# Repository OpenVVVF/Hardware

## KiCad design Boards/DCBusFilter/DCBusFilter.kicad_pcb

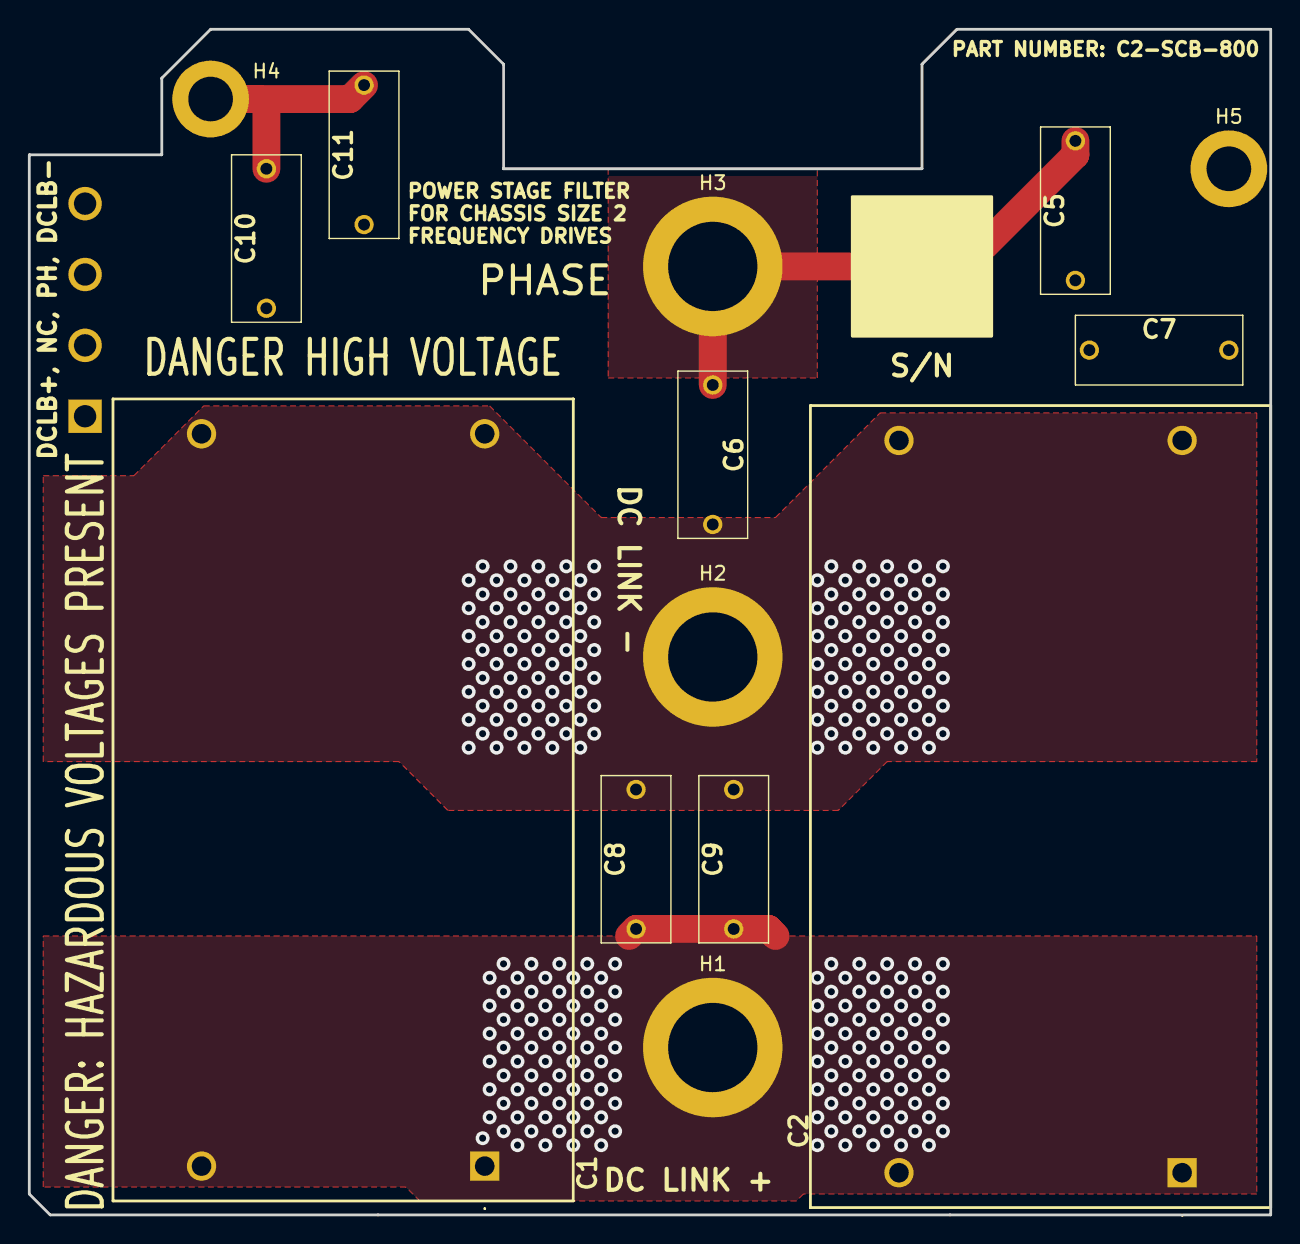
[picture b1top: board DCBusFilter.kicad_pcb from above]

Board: 4 copper layers, 89.0 x 85.0 mm, 15 parts (1 on the bottom side), 5 nets.

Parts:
C1, C2: MKP1848S61010JY5B
C5, C6, C7, C8, C9, C10, C11: VY1222M47Y5UQ6TV0
H1, H2, H3: MountingHole_Pad; MountingHole_6.4mm_M6_ISO14580_Pad
H4, H5: MountingHole_Pad; MountingHole_3.2mm_M3_ISO14580_Pad
J1: TBP01R2-508-04BE; SHDR4W100P0X508_1X4_2192X850X1200P

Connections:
/CHASSIS_GND: C10.1, C11.1, H4.1
/CHASSIS_GND_1: C7.1, H5.1
/DC_LINK_+: C1.1, C1.3, C2.1, C2.3, C5.2, C7.2, C8.2, C9.2, H1.1, J1.1
/DC_LINK_-: C1.2, C1.4, C2.2, C2.4, C6.1, C8.1, C9.1, C10.2, H2.1, J1.4
/PHASE_LEG: C5.1, C6.2, C11.2, H3.1, J1.3

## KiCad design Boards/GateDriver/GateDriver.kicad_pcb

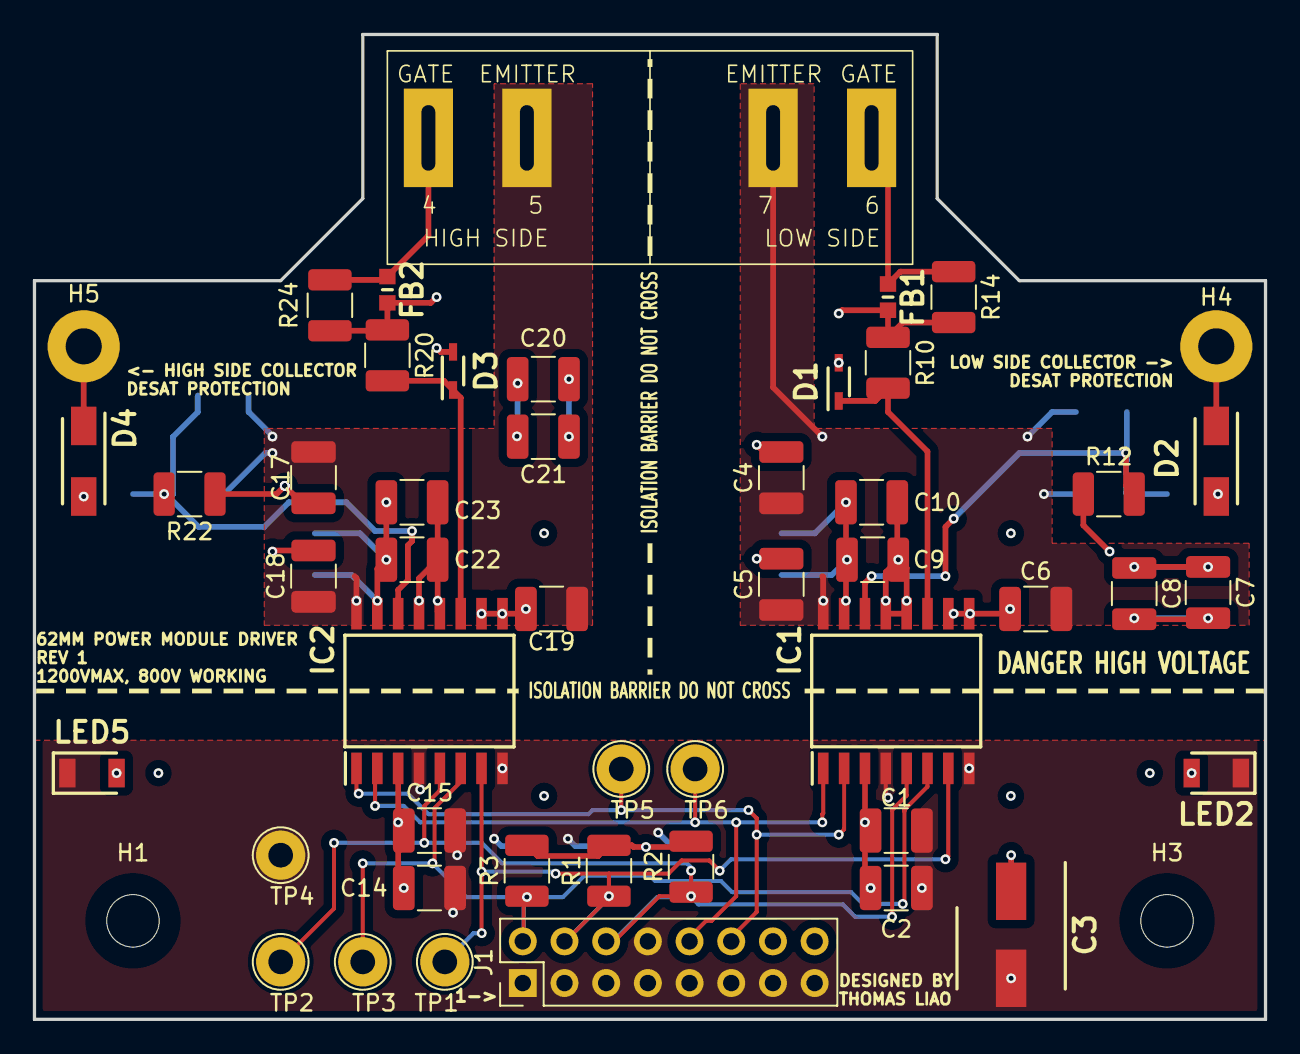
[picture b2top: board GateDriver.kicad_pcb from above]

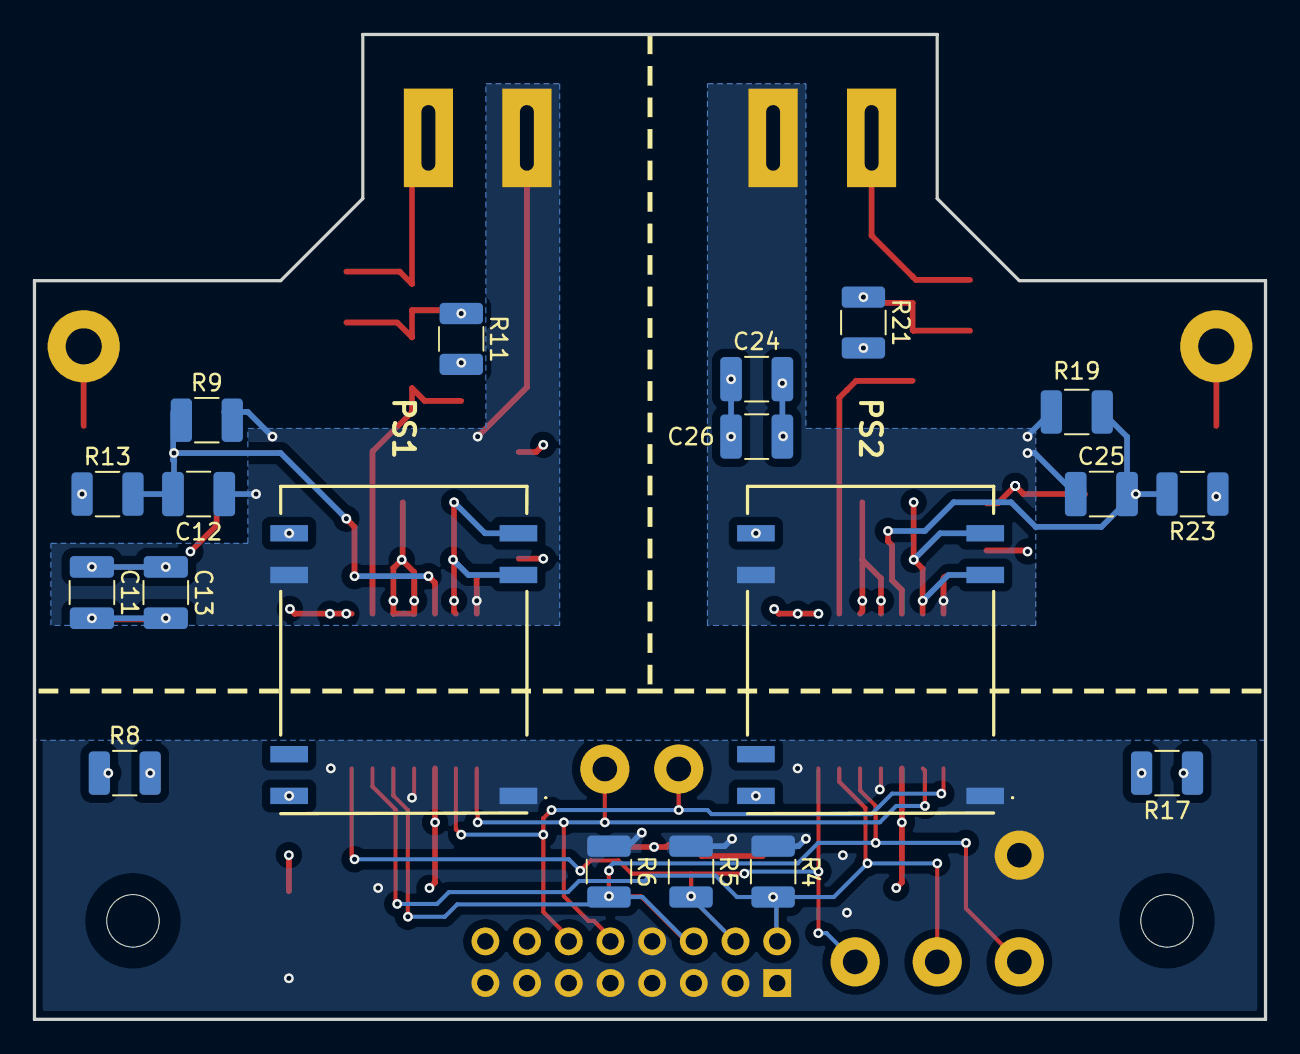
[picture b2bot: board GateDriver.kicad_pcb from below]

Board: 6 copper layers, 75.0 x 60.0 mm, 69 parts (19 on the bottom side), 30 nets.

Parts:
C1, C5, C6, C9, C12, C14, C18, C19, C22, C25: 100nF; C_1210_3225Metric_Pad1.33x2.70mm_HandSolder
C2, C4, C7, C8, C10, C11, C13, C15, C17, C20, C21, C23, C24, C26: 10uF; C_1210_3225Metric_Pad1.33x2.70mm_HandSolder
C3: UCM1H101MCL1GS; CAPAE660X800N
D1, D3: BAT54WS-7-F; SOD2513X120N
D2, D4: FM2000GP-TP; DIOM5226X244N
FB1, FB2: FBMJ1608HS220NTR; BEADC1608X100N
H1, H3: MountingHole; MountingHole_3.2mm_M3
H4, H5: MountingHole_Pad; MountingHole_2.2mm_M2_Pad
IC1, IC2: ADUM4136BRWZ; SOIC127P1032X265-16N
J1: Conn_02x08_Counter_Clockwise; PinHeader_2x08_P2.54mm_Vertical
LED2: LTST-C230CKT; LEDC3216X120N
LED5: LTST-C230GKT; LEDC3216X120N
PS1, PS2: MGJ2D121509MPC-R7; MGJ2D121509MPCR7
Q1: 62mm_power_module
R1, R2, R3, R4, R5, R6, R17: 4.7k; R_1210_3225Metric_Pad1.30x2.65mm_HandSolder
R8: 220; R_1210_3225Metric_Pad1.30x2.65mm_HandSolder
R9, R14, R19, R24: 0; R_1210_3225Metric_Pad1.30x2.65mm_HandSolder
R10, R20: 9.1; R_1210_3225Metric_Pad1.30x2.65mm_HandSolder
R11, R21: 6.8; R_1210_3225Metric_Pad1.30x2.65mm_HandSolder
R12, R13, R22, R23: 1k; R_1210_3225Metric_Pad1.30x2.65mm_HandSolder
TP1, TP2, TP3, TP4, TP5, TP6: TestPoint; TestPoint_Loop_D2.54mm_Drill1.5mm_Beaded

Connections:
/+3.3V_A: C1.2, C2.1, C14.2, C15.1, IC1.3 (VDD1), IC2.3 (VDD1), J1.14, R1.2, R2.2, R3.2, R8.2
/+12V_A: C3.1 (+), J1.16, PS1.8 (+VIN), PS2.8 (+VIN), R17.2
/FAULT: IC1.6 (~FAULT), IC2.6 (~FAULT), J1.2, R3.1, R4.2, TP3.1
/GND_A: C1.1, C2.2, C3.2 (-), C14.1, C15.2, IC1.4 (VSS1_1), IC1.8 (VSS1_2), IC2.4 (VSS1_1), IC2.8 (VSS1_2), J1.1, J1.3, J1.5, J1.7, J1.8, J1.9, J1.11, J1.13, J1.15, LED2.1 (K), LED5.1 (K), PS1.1 (-VIN), PS2.1 (-VIN), R4.1, R5.1, R6.1, TP4.1
/PH_H: IC1.2 (VI-), IC2.1 (VI+), J1.12, TP5.1
/PH_H_C: D4.1 (K), H5.1
/PH_H_G: FB2.1, Q1.3 (HIGH_GATE), R24.1
/PH_L: IC1.1 (VI+), IC2.2 (VI-), J1.10, TP6.1
/PH_L_C: D2.1 (K), H4.1
/PH_L_G: FB1.1, Q1.1 (LOW_GATE), R14.1
/READY: IC1.7 (READY), IC2.7 (READY), J1.4, R1.1, R5.2, TP1.1
/RESET: IC1.5 (~RESET), IC2.5 (~RESET), J1.6, R2.1, R6.2, TP2.1
/SingleChannelDriver1/+15V_B: C4.2, C5.2, C7.1, C8.1, C9.2, C10.1, C11.1, C13.1, IC1.12 (VDD2_1), IC1.13 (VDD2_2), PS1.5 (+VOUT), R12.1
/SingleChannelDriver1/-9V_B: C6.1, C7.2, C8.2, C9.1, C10.2, C11.2, C13.2, IC1.9 (VSS2_1), IC1.10 (VSS2_2), IC1.15 (VSS2_3), PS1.3 (-VOUT_1), PS1.4 (-VOUT_2)
/SingleChannelDriver1/GND_B: C4.1, C5.1, C6.2, C12.1, IC1.16 (GND2), PS1.6 (0V), Q1.2 (LOW_EMITTER), R9.2
/SingleChannelDriver/+15V_B: C17.2, C18.2, C20.1, C21.1, C22.2, C23.1, C24.1, C26.1, IC2.12 (VDD2_1), IC2.13 (VDD2_2), PS2.5 (+VOUT), R22.1
/SingleChannelDriver/-9V_B: C19.1, C20.2, C21.2, C22.1, C23.2, C24.2, C26.2, IC2.9 (VSS2_1), IC2.10 (VSS2_2), IC2.15 (VSS2_3), PS2.3 (-VOUT_1), PS2.4 (-VOUT_2)
/SingleChannelDriver/GND_B: C17.1, C18.1, C19.2, C25.1, IC2.16 (GND2), PS2.6 (0V), Q1.4 (HIGH_EMITTER), R19.2
unnamed: D1.2 (A), R11.2
unnamed: D1.1 (K), IC1.11 (VOUT), R10.2
unnamed: D2.2 (A), R13.1
unnamed: D3.2 (A), R21.2
unnamed: D3.1 (K), IC2.11 (VOUT), R20.2
unnamed: D4.2 (A), R23.1
unnamed: FB1.2, R10.1, R11.1, R14.2
unnamed: FB2.2, R20.1, R21.1, R24.2
unnamed: C12.2, IC1.14 (DESAT), R9.1, R12.2, R13.2
unnamed: C25.2, IC2.14 (DESAT), R19.1, R22.2, R23.2
unnamed: LED2.2 (A), R8.1
unnamed: LED5.2 (A), R17.1

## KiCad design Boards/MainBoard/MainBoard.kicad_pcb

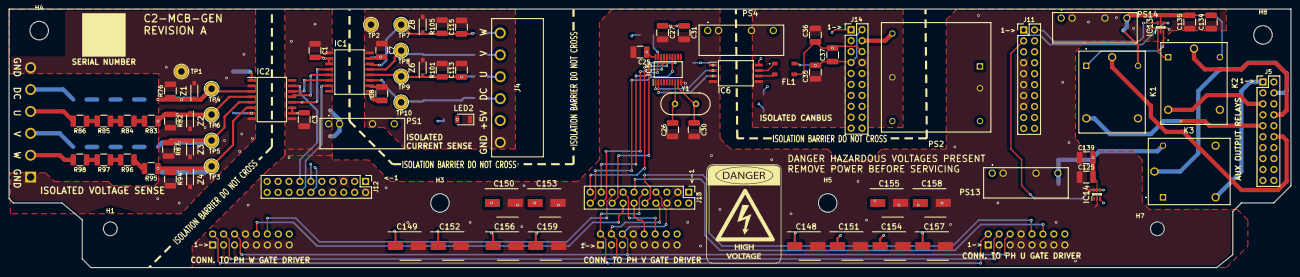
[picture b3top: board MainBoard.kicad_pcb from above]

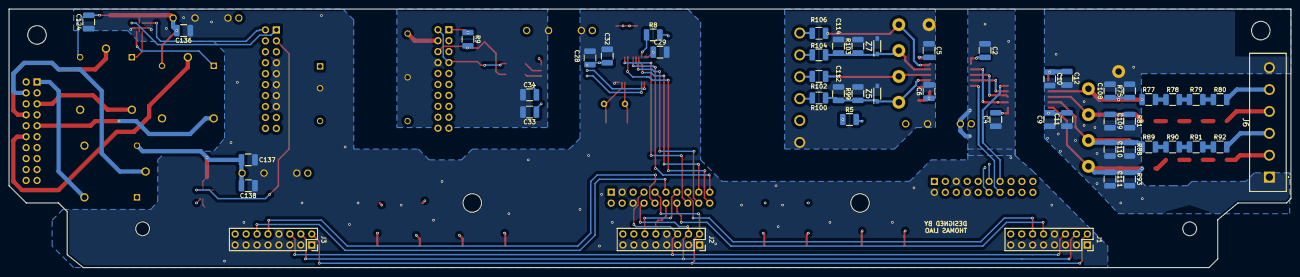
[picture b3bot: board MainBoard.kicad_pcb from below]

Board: 6 copper layers, 297.5 x 60.0 mm, 139 parts (50 on the bottom side), 85 nets.

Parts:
C1, C3, C5, C6, C9, C10, C25, C31, C32, C34: 100nF; C_1210_3225Metric_Pad1.33x2.70mm_HandSolder
C2, C4, C7, C8, C11, C12: 1uF; C_1210_3225Metric_Pad1.33x2.70mm_HandSolder
C26, C30, C35, C36, C37: 22pF; C_1210_3225Metric_Pad1.33x2.70mm_HandSolder
C27, C28, C29, C33, C124, C125, C134, C135, C136, C137, C138, C139: 10uF; C_1210_3225Metric_Pad1.33x2.70mm_HandSolder
C108, C109, C110, C111, C112, C113, C114, C115: 10nF; C_1210_3225Metric_Pad1.33x2.70mm_HandSolder
C148, C149, C150, C151, C152, C153, C154, C155, C156, C157, C158, C159: UCM1H101MCL1GS; CAPAE660X800N
FL1: ACT45B-101-2P-TL003; ACT45B1012PTL003
H1, H7: MountingHole; MountingHole_3.2mm_M3
H3, H4, H5, H8: MountingHole; MountingHole_4.3mm_M4
IC1, IC2: MAX22530AWE+; SOIC127P1032X265-16N
IC5: MCP2515-e_ST; SOP65P640X120-20N
IC6: ISO1042BDWVR; SOIC127P1150X280-8N
IC13, IC14: DRDNB21D-7; SOT65P210X110-6N
J1, J2, J3: Conn_02x08_Counter_Clockwise; PinSocket_2x08_P2.54mm_Vertical
J4: TBP01R1-508-06BE; TBP01R150806BE
J5, J11, J12, J13, J14: Conn_02x10_Counter_Clockwise; PinHeader_2x10_P2.54mm_Vertical
J6: TBP01R2-508-06BE; TBP01R250806BE
K1, K2, K3: AWHSH105D00G
LED2: LTST-C230CKT; LEDC3216X120N
PS1, PS4, PS13, PS14: RKE-1205S_H; RKE1205SH
PS2: REC10K-2424DAW_H2; REC10K-AW
R5, R76, R82, R88, R94, R99, R101, R103, R105: 1k; R_1210_3225Metric_Pad1.30x2.65mm_HandSolder
R8: 4.7k; R_1210_3225Metric_Pad1.30x2.65mm_HandSolder
R9: 120; R_1210_3225Metric_Pad1.30x2.65mm_HandSolder
R75, R81, R87, R93: 2k; R_1210_3225Metric_Pad1.30x2.65mm_HandSolder
R77, R78, R79, R80, R83, R84, R85, R86, R89, R90, R91, R92, R95, R96, R97, R98: 250k; R_1210_3225Metric_Pad1.30x2.65mm_HandSolder
R100, R102, R104, R106: 5k; R_1210_3225Metric_Pad1.30x2.65mm_HandSolder
TP1, TP2, TP3, TP4, TP5, TP6, TP7, TP8, TP9, TP10: TestPoint; TestPoint_Loop_D2.54mm_Drill1.5mm_Beaded
Y1: 8MHz; Crystal_HC49-4H_Vertical
Z1, Z2, Z3, Z4, Z5, Z6, Z7, Z8: SZMMSZ4678T1G; SOD3716X135N

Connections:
/+3.3V_A: C1.2, C2.2, C3.2, C4.2, C25.1, C28.2, C29.1, C32.1, C148.1 (+), C149.1 (+), C150.1 (+), C151.1 (+), IC1.10 (VDDPL), IC1.11 (VDDL), IC2.10 (VDDPL), IC2.11 (VDDL), IC5.20 (VDD), IC6.1 (VCC1), J1.14, J2.14, J3.14, J12.1, J12.4, J12.7, J13.1, J13.4, R8.2
/+5V_Y: J4.5, PS1.7 (+VOUT), R5.2
/+12V_A: C27.1, C31.1, C152.1 (+), C153.1 (+), C154.1 (+), C155.1 (+), C156.1 (+), C157.1 (+), C158.1 (+), C159.1 (+), J1.16, J2.16, J3.16, J11.6, J11.8, J11.10, J11.12, J11.14, J12.3, J12.6, J12.9, J13.2, J13.5, PS1.1 (+VIN), PS2.1 (+VIN), PS4.1 (+VIN), PS13.1 (+VIN), PS14.1 (+VIN)
/ADC_1/ADC2_5VFILTER_1/OUT: C112.1, IC1.3 (AIN1), R99.1, R100.1, TP10.1, Z5.1 (K)
/ADC_1/ADC2_5VFILTER_2/OUT: C113.1, IC1.4 (AIN2), R101.1, R102.1, TP9.1, Z6.1 (K)
/ADC_1/ADC2_5VFILTER_3/OUT: C114.1, IC1.5 (AIN3), R103.1, R104.1, TP8.1, Z7.1 (K)
/ADC_1/ADC2_5VFILTER_4/OUT: C115.1, IC1.6 (AIN4), R105.1, R106.1, TP7.1, Z8.1 (K)
/ADC_1/VoltageSenseInputStage1/LV_OUT: C109.1, IC2.4 (AIN2), R81.1, R82.1, R83.1, TP6.1, Z2.1 (K)
/ADC_1/VoltageSenseInputStage2/LV_OUT: C110.1, IC2.5 (AIN3), R87.1, R88.1, R89.1, TP5.1, Z3.1 (K)
/ADC_1/VoltageSenseInputStage3/LV_OUT: C111.1, IC2.6 (AIN4), R93.1, R94.1, R95.1, TP3.1, Z4.1 (K)
/ADC_1/VoltageSenseInputStage/LV_OUT: C108.1, IC2.3 (AIN1), R75.1, R76.1, R77.1, TP4.1, Z1.1 (K)
/CAN_5V_OUT: C33.1, C34.2, IC6.8 (VCC2), PS4.7 (+VOUT)
/CAN_24V_OUT: J14.4, PS2.6 (+VOUT)
/CAN_GND: C33.2, C34.1, C35.1, C36.2, IC6.5 (GND2), J14.8, PS2.5 (COM), PS4.5 (-VOUT)
/CAN_HIGH: C35.2, C37.1, FL1.4, J14.2, J14.7
/CAN_JUMPER_B: J14.1, R9.1
/CAN_LOW: C36.1, C37.2, FL1.3, J14.6, R9.2
/DC_LINK_VSENSE_U: J6.5, R80.2
/FAULT: J1.2, J2.2, J3.2, J13.9
/GND_A: C1.1, C2.1, C3.1, C4.1, C25.2, C26.2, C27.2, C28.1, C29.2, C30.2, C31.2, C32.2, C124.1, C125.1, C134.1, C135.1, C136.1, C137.1, C138.1, C139.1, C148.2 (-), C149.2 (-), C150.2 (-), C151.2 (-), C152.2 (-), C153.2 (-), C154.2 (-), C155.2 (-), C156.2 (-), C157.2 (-), C158.2 (-), C159.2 (-), IC1.9 (GNDL), IC2.9 (GNDL), IC5.10 (VSS), IC6.4 (GND1), IC13.2 (E1/E2), IC14.2 (E1/E2), IC14.6 (B1), J1.1, J1.3, J1.5, J1.7, J1.8, J1.9, J1.11, J1.13, J1.15, J2.1, J2.3, J2.5, J2.7, J2.8, J2.9, J2.11, J2.13, J2.15, J3.1, J3.3, J3.5, J3.7, J3.8, J3.9, J3.11, J3.13, J3.15, J11.7, J11.9, J11.11, J11.13, J11.15, J12.2, J12.5, J12.8, J13.3, J13.6, PS1.2 (-VIN), PS2.2 (-VIN), PS4.2 (-VIN), PS13.2 (-VIN), PS13.5 (-VOUT), PS14.2 (-VIN), PS14.5 (-VOUT)
/GND_U: C9.1, C10.2, C11.1, C12.2, C108.2, C109.2, C110.2, C111.2, IC2.2 (AGND), IC2.8 (GNDF), J6.1, J6.6, R75.2, R76.2, R81.2, R82.2, R87.2, R88.2, R93.2, R94.2, TP1.1, Z1.2 (A), Z2.2 (A), Z3.2 (A), Z4.2 (A)
/ISENSE_DC_LINK_Y: J4.4, R100.2
/ISENSE_GND_Y: C5.1, C6.2, C7.1, C8.2, C112.2, C113.2, C114.2, C115.2, IC1.2 (AGND), IC1.8 (GNDF), J4.6, LED2.1 (K), PS1.5 (-VOUT), R99.2, R101.2, R103.2, R105.2, TP2.1, Z5.2 (A), Z6.2 (A), Z7.2 (A), Z8.2 (A)
/ISENSE_PH_U_Y: J4.3, R102.2
/ISENSE_PH_V_Y: J4.2, R104.2
/ISENSE_PH_W_Y: J4.1, R106.2
/OutputRelays/+5V_A_INT: C125.2, C137.2, C138.2, C139.2, IC14.5 (K1/K2), K3.4 (COIL_2), PS13.7 (+VOUT)
/OutputRelays/+5V_A_INT_2: C124.2, C134.2, C135.2, C136.2, IC13.5 (K1/K2), K1.4 (COIL_2), K2.4 (COIL_2), PS14.7 (+VOUT)
/PH_U_H: J1.12, J13.15
/PH_U_L: J1.10, J13.14
/PH_U_VSENSE_U: J6.4, R86.2
/PH_V_H: J2.12, J13.13
/PH_V_L: J2.10, J13.12
/PH_V_VSENSE_U: J6.3, R92.2
/PH_W_H: J3.12, J13.11
/PH_W_L: J3.10, J13.10
/PH_W_VSENSE_U: J6.2, R98.2
/READY: J1.4, J2.4, J3.4, J13.8
/RELAY1_COM: J5.12, K1.5 (COM)
/RELAY1_NO: J5.9, K1.2 (NO)
/RELAY2_COM: J5.8, K2.5 (COM)
/RELAY2_NO: J5.5, K2.2 (NO)
/RELAY3_COM: J5.4, K3.5 (COM)
/RELAY3_NO: J5.1, K3.2 (NO)
/RELAY_1_A: IC13.4 (B2), J11.1
/RELAY_2_A: IC13.6 (B1), J11.2
/RELAY_3_A: IC14.4 (B2), J11.3
/RESET: J1.6, J2.6, J3.6, J13.7
/SPI1_CAN_CS_A: IC5.18 (~CS), J13.17
/SPI1_CAN_INT_A: IC5.13 (~INT), J13.16
/SPI1_RX_A: IC5.17 (SO), J13.18
/SPI1_SCK_A: IC5.14 (SCK), J13.20
/SPI1_TX_A: IC5.16 (SI), J13.19
/SPI2_ADC1_CS_A: IC2.15 (~CS), J12.13
/SPI2_ADC2_CS_A: IC1.15 (~CS), J12.14
/SPI2_RX_A: IC1.12 (SDO), IC2.12 (SDO), J12.10
/SPI2_SCK_A: IC1.14 (SCLK), IC2.14 (SCLK), J12.12
/SPI2_TX_A: IC1.13 (SDI), IC2.13 (SDI), J12.11
unnamed: C6.1, C8.1, IC1.1 (REF)
unnamed: C5.2, C7.2, IC1.7 (VDDF)
unnamed: C10.1, C12.1, IC2.1 (REF)
unnamed: C9.2, C11.2, IC2.7 (VDDF)
unnamed: C30.1, IC5.9 (OSC1), Y1.2
unnamed: C26.1, IC5.8 (OSC2), Y1.1
unnamed: IC5.2 (RXCAN), IC6.3 (RXD)
unnamed: IC5.1 (TXCAN), IC6.2 (TXD)
unnamed: IC5.19 (~RESET), R8.1
unnamed: FL1.1, IC6.7 (CANH)
unnamed: FL1.2, IC6.6 (CANL)
unnamed: IC13.1 (C1/A1), K2.1 (COIL_1)
unnamed: IC13.3 (C2/A2), K1.1 (COIL_1)
unnamed: IC14.3 (C2/A2), K3.1 (COIL_1)
unnamed: LED2.2 (A), R5.1
unnamed: R77.2, R78.1
unnamed: R78.2, R79.1
unnamed: R79.2, R80.1
unnamed: R83.2, R84.1
unnamed: R84.2, R85.1
unnamed: R85.2, R86.1
unnamed: R89.2, R90.1
unnamed: R90.2, R91.1
unnamed: R91.2, R92.1
unnamed: R95.2, R96.1
unnamed: R96.2, R97.1
unnamed: R97.2, R98.1

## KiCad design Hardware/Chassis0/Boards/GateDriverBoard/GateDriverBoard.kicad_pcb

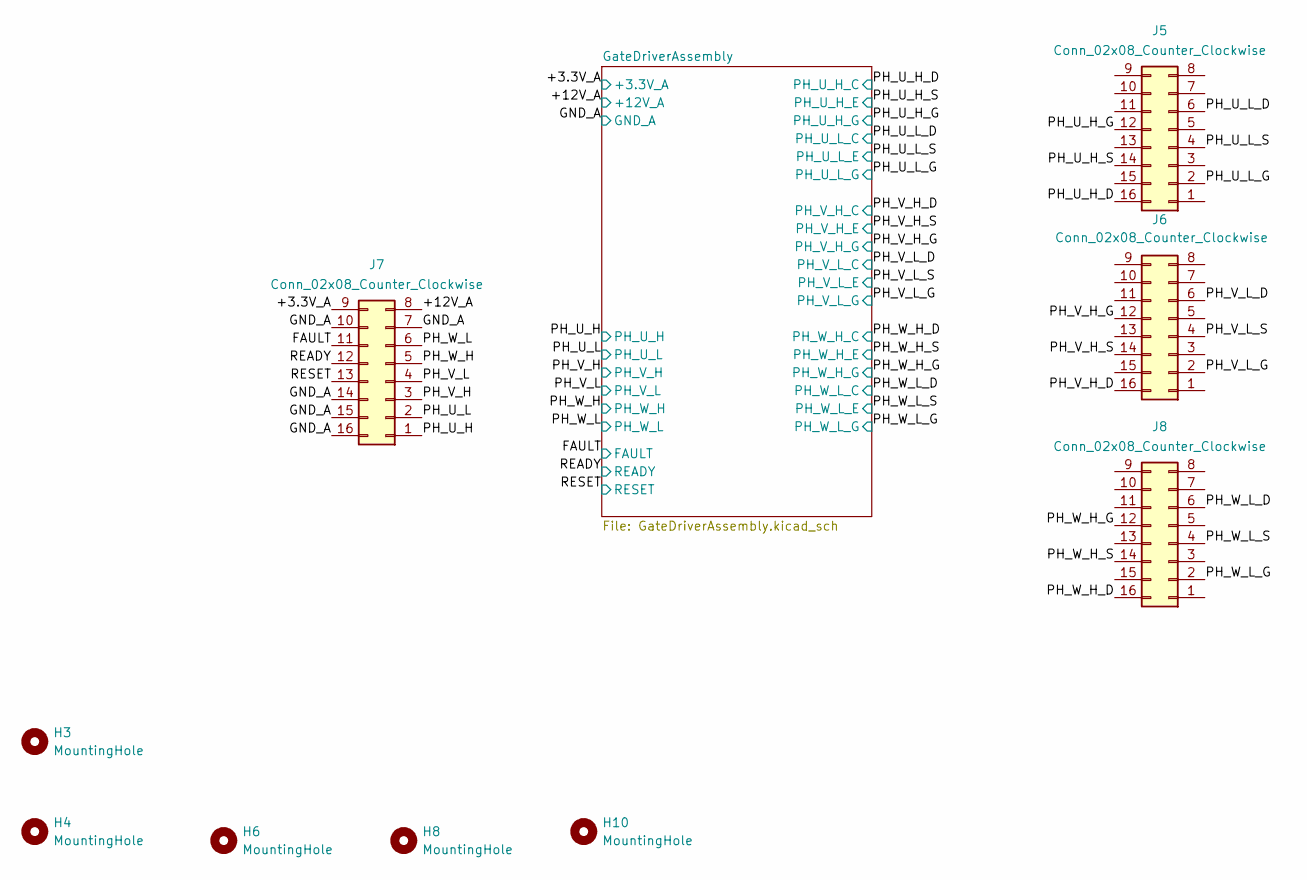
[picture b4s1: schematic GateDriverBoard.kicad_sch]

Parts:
H3, H4, H6, H8, H10: MountingHole; MountingHole_4.3mm_M4
J5, J6, J7, J8: Conn_02x08_Counter_Clockwise; PinSocket_2x08_P2.54mm_Vertical

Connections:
/+3.3V_A: J7.9; also elsewhere on the board
/+12V_A: J7.8; also elsewhere on the board
/FAULT: J7.11; also elsewhere on the board
/GND_A: J7.7, J7.10, J7.14, J7.15, J7.16; also elsewhere on the board
/PH_U_H: J7.1; also elsewhere on the board
/PH_U_H_D: J5.16; also elsewhere on the board
/PH_U_H_G: J5.12; also elsewhere on the board
/PH_U_H_S: J5.14; also elsewhere on the board
/PH_U_L: J7.2; also elsewhere on the board
/PH_U_L_D: J5.6; also elsewhere on the board
/PH_U_L_G: J5.2; also elsewhere on the board
/PH_U_L_S: J5.4; also elsewhere on the board
/PH_V_H: J7.3; also elsewhere on the board
/PH_V_H_D: J6.16; also elsewhere on the board
/PH_V_H_G: J6.12; also elsewhere on the board
/PH_V_H_S: J6.14; also elsewhere on the board
/PH_V_L: J7.4; also elsewhere on the board
/PH_V_L_D: J6.6; also elsewhere on the board
/PH_V_L_G: J6.2; also elsewhere on the board
/PH_V_L_S: J6.4; also elsewhere on the board
/PH_W_H: J7.5; also elsewhere on the board
/PH_W_H_D: J8.16; also elsewhere on the board
/PH_W_H_G: J8.12; also elsewhere on the board
/PH_W_H_S: J8.14; also elsewhere on the board
/PH_W_L: J7.6; also elsewhere on the board
/PH_W_L_D: J8.6; also elsewhere on the board
/PH_W_L_G: J8.2; also elsewhere on the board
/PH_W_L_S: J8.4; also elsewhere on the board
/READY: J7.12; also elsewhere on the board
/RESET: J7.13; also elsewhere on the board

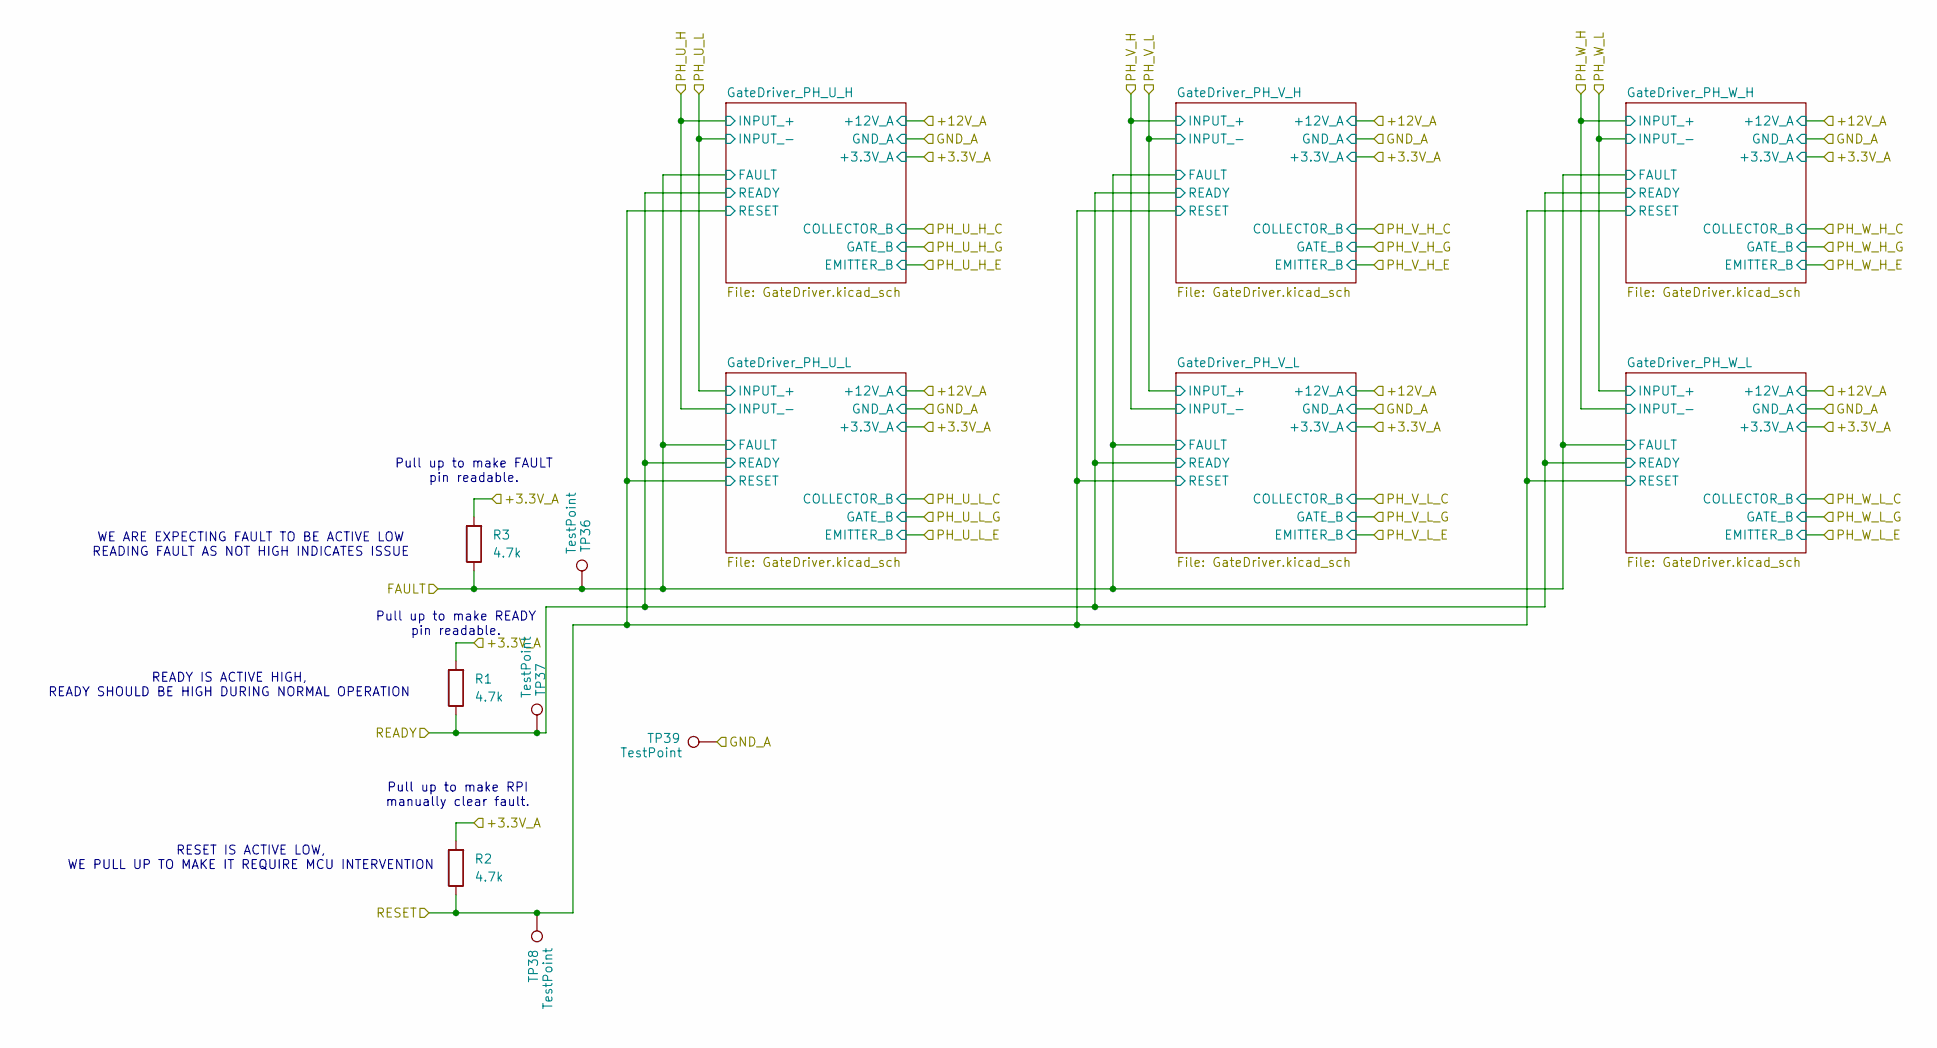
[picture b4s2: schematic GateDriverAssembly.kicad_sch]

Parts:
R1, R2, R3: 4.7k; R_1210_3225Metric_Pad1.30x2.65mm_HandSolder
TP36, TP37, TP38, TP39: TestPoint; TestPoint_Loop_D2.54mm_Drill1.5mm_Beaded

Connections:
/+3.3V_A: R1.2, R2.2, R3.2; also elsewhere on the board
/FAULT: R3.1, TP36.1; also elsewhere on the board
/GND_A: TP39.1; also elsewhere on the board
/READY: R1.1, TP37.1; also elsewhere on the board
/RESET: R2.1, TP38.1; also elsewhere on the board

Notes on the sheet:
READY IS ACTIVE HIGH, READY SHOULD BE HIGH DURING NORMAL OPERATION
Pull up to make READY pin readable.
WE ARE EXPECTING FAULT TO BE ACTIVE LOW READING FAULT AS NOT HIGH INDICATES ISSUE
Pull up to make FAULT pin readable.
Pull up to make RPI manually clear fault.
RESET IS ACTIVE LOW, WE PULL UP TO MAKE IT REQUIRE MCU INTERVENTION

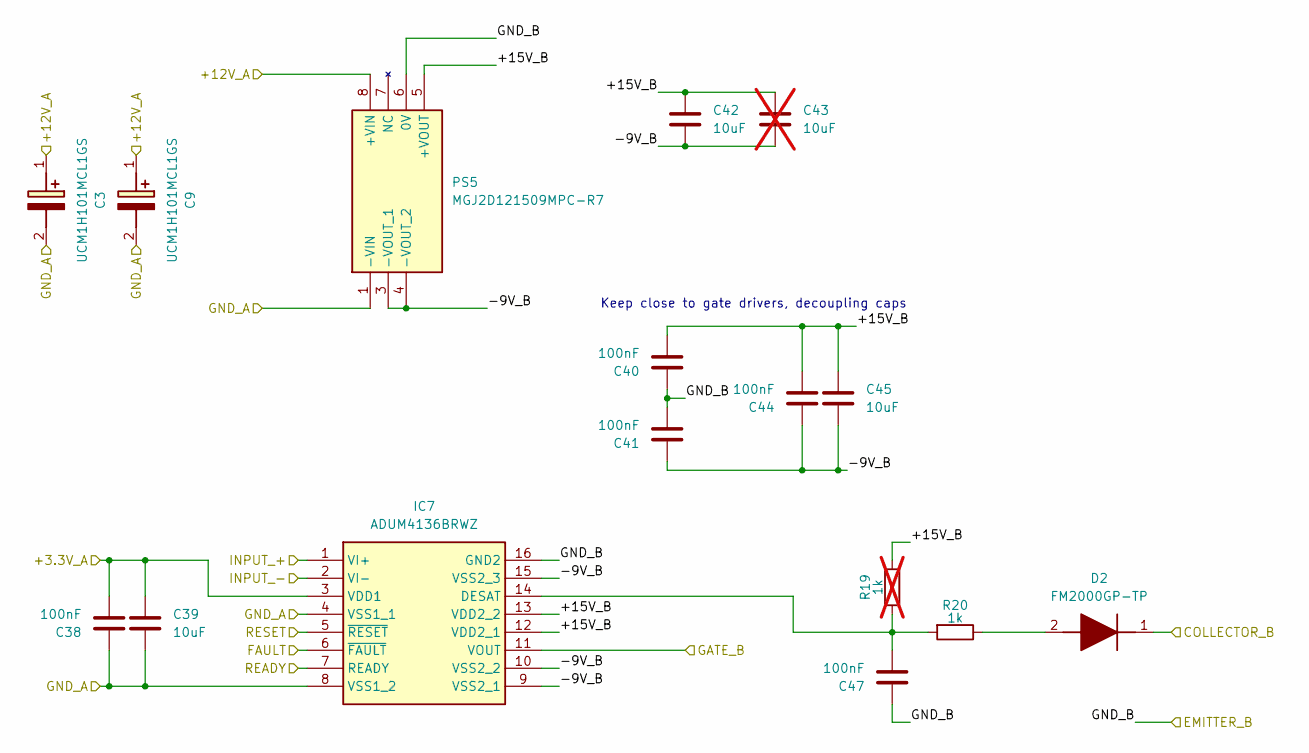
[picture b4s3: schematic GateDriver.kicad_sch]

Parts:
C3, C9: UCM1H101MCL1GS; CAPAE660X800N; Mouser Part Number 647-UCM1H101MCL1GS
C38, C40, C41, C44, C47: 100nF; C_1210_3225Metric_Pad1.33x2.70mm_HandSolder
C39, C42, C45: 10uF; C_1210_3225Metric_Pad1.33x2.70mm_HandSolder
C43: 10uF; C_1210_3225Metric_Pad1.33x2.70mm_HandSolder; not fitted
D2: FM2000GP-TP; DIOM5226X244N; Mouser Part Number 833-FM2000GP-TP
IC7: ADUM4136BRWZ; SOIC127P1032X265-16N; Mouser Part Number 584-ADUM4136BRWZ
PS5: MGJ2D121509MPC-R7; MGJ2D121509MPCR7; Mouser Part Number 580-MGJ2D121509MPCR7
R19: 1k; R_1210_3225Metric_Pad1.30x2.65mm_HandSolder; not fitted
R20: 1k; R_1210_3225Metric_Pad1.30x2.65mm_HandSolder

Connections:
/+3.3V_A: C38.2, C39.1, IC7.3 (VDD1); also elsewhere on the board
/+12V_A: C3.1 (+), C9.1 (+), PS5.8 (+VIN); also elsewhere on the board
/FAULT: IC7.6 (~FAULT); also elsewhere on the board
/GND_A: C3.2 (-), C9.2 (-), C38.1, C39.2, IC7.4 (VSS1_1), IC7.8 (VSS1_2), PS5.1 (-VIN); also elsewhere on the board
/GateDriverAssembly/GateDriver_PH_U_H/+15V_B: C40.2, C42.1, C43.1, C44.2, C45.1, IC7.12 (VDD2_1), IC7.13 (VDD2_2), PS5.5 (+VOUT), R19.1
/GateDriverAssembly/GateDriver_PH_U_H/-9V_B: C41.1, C42.2, C43.2, C44.1, C45.2, IC7.9 (VSS2_1), IC7.10 (VSS2_2), IC7.15 (VSS2_3), PS5.3 (-VOUT_1), PS5.4 (-VOUT_2)
/PH_U_H: IC7.1 (VI+); also elsewhere on the board
/PH_U_H_D: D2.1 (K); also elsewhere on the board
/PH_U_H_G: IC7.11 (VOUT); also elsewhere on the board
/PH_U_H_S: C40.1, C41.2, C47.1, IC7.16 (GND2), PS5.6 (0V); also elsewhere on the board
/PH_U_L: IC7.2 (VI-); also elsewhere on the board
/READY: IC7.7 (READY); also elsewhere on the board
/RESET: IC7.5 (~RESET); also elsewhere on the board
unnamed: D2.2 (A), R20.1
unnamed: C47.2, IC7.14 (DESAT), R19.2, R20.2

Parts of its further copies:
C4, C5, C6, C7, C8, C10, C11, C12, C13, C14: UCM1H101MCL1GS; CAPAE660X800N; Mouser Part Number 647-UCM1H101MCL1GS
C53, C55, C56, C59, C62, C64, C66, C67, C70, C73, C75, C77, C78, C81, C84, C86, C88, C89, C92, C95, C97, C99, C100, C103, C106: 100nF; C_1210_3225Metric_Pad1.33x2.70mm_HandSolder
C54, C57, C60, C65, C68, C71, C76, C79, C82, C87, C90, C93, C98, C101, C104: 10uF; C_1210_3225Metric_Pad1.33x2.70mm_HandSolder
C58, C69, C80, C91, C102: 10uF; C_1210_3225Metric_Pad1.33x2.70mm_HandSolder; not fitted
D7, D9, D11, D13, D14: FM2000GP-TP; DIOM5226X244N; Mouser Part Number 833-FM2000GP-TP
IC8, IC9, IC10, IC11, IC12: ADUM4136BRWZ; SOIC127P1032X265-16N; Mouser Part Number 584-ADUM4136BRWZ
PS8, PS9, PS10, PS11, PS12: MGJ2D121509MPC-R7; MGJ2D121509MPCR7; Mouser Part Number 580-MGJ2D121509MPCR7
R30, R40, R50, R60, R70: 1k; R_1210_3225Metric_Pad1.30x2.65mm_HandSolder; not fitted
R31, R41, R51, R61, R71: 1k; R_1210_3225Metric_Pad1.30x2.65mm_HandSolder

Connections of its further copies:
/+3.3V_A: C53.2, C54.1, C64.2, C65.1, C75.2, C76.1, C86.2, C87.1, C97.2, C98.1, IC8.3 (VDD1), IC9.3 (VDD1), IC10.3 (VDD1), IC11.3 (VDD1), IC12.3 (VDD1); also elsewhere on the board
/+12V_A: C4.1 (+), C5.1 (+), C6.1 (+), C7.1 (+), C8.1 (+), C10.1 (+), C11.1 (+), C12.1 (+), C13.1 (+), C14.1 (+), PS8.8 (+VIN), PS9.8 (+VIN), PS10.8 (+VIN), PS11.8 (+VIN), PS12.8 (+VIN); also elsewhere on the board
/FAULT: IC8.6 (~FAULT), IC9.6 (~FAULT), IC10.6 (~FAULT), IC11.6 (~FAULT), IC12.6 (~FAULT); also elsewhere on the board
/GND_A: C4.2 (-), C5.2 (-), C6.2 (-), C7.2 (-), C8.2 (-), C10.2 (-), C11.2 (-), C12.2 (-), C13.2 (-), C14.2 (-), C53.1, C54.2, C64.1, C65.2, C75.1, C76.2, C86.1, C87.2, C97.1, C98.2, IC8.4 (VSS1_1), IC8.8 (VSS1_2), IC9.4 (VSS1_1), IC9.8 (VSS1_2), IC10.4 (VSS1_1), IC10.8 (VSS1_2), IC11.4 (VSS1_1), IC11.8 (VSS1_2), IC12.4 (VSS1_1), IC12.8 (VSS1_2), PS8.1 (-VIN), PS9.1 (-VIN), PS10.1 (-VIN), PS11.1 (-VIN), PS12.1 (-VIN); also elsewhere on the board
/GateDriverAssembly/GateDriver_PH_U_L/+15V_B: C55.2, C57.1, C58.1, C59.2, C60.1, IC8.12 (VDD2_1), IC8.13 (VDD2_2), PS8.5 (+VOUT), R30.1
/GateDriverAssembly/GateDriver_PH_U_L/-9V_B: C56.1, C57.2, C58.2, C59.1, C60.2, IC8.9 (VSS2_1), IC8.10 (VSS2_2), IC8.15 (VSS2_3), PS8.3 (-VOUT_1), PS8.4 (-VOUT_2)
/GateDriverAssembly/GateDriver_PH_V_H/+15V_B: C66.2, C68.1, C69.1, C70.2, C71.1, IC9.12 (VDD2_1), IC9.13 (VDD2_2), PS9.5 (+VOUT), R40.1
/GateDriverAssembly/GateDriver_PH_V_H/-9V_B: C67.1, C68.2, C69.2, C70.1, C71.2, IC9.9 (VSS2_1), IC9.10 (VSS2_2), IC9.15 (VSS2_3), PS9.3 (-VOUT_1), PS9.4 (-VOUT_2)
/GateDriverAssembly/GateDriver_PH_V_L/+15V_B: C77.2, C79.1, C80.1, C81.2, C82.1, IC10.12 (VDD2_1), IC10.13 (VDD2_2), PS10.5 (+VOUT), R50.1
/GateDriverAssembly/GateDriver_PH_V_L/-9V_B: C78.1, C79.2, C80.2, C81.1, C82.2, IC10.9 (VSS2_1), IC10.10 (VSS2_2), IC10.15 (VSS2_3), PS10.3 (-VOUT_1), PS10.4 (-VOUT_2)
/GateDriverAssembly/GateDriver_PH_W_H/+15V_B: C88.2, C90.1, C91.1, C92.2, C93.1, IC11.12 (VDD2_1), IC11.13 (VDD2_2), PS11.5 (+VOUT), R60.1
/GateDriverAssembly/GateDriver_PH_W_H/-9V_B: C89.1, C90.2, C91.2, C92.1, C93.2, IC11.9 (VSS2_1), IC11.10 (VSS2_2), IC11.15 (VSS2_3), PS11.3 (-VOUT_1), PS11.4 (-VOUT_2)
/GateDriverAssembly/GateDriver_PH_W_L/+15V_B: C99.2, C101.1, C102.1, C103.2, C104.1, IC12.12 (VDD2_1), IC12.13 (VDD2_2), PS12.5 (+VOUT), R70.1
/GateDriverAssembly/GateDriver_PH_W_L/-9V_B: C100.1, C101.2, C102.2, C103.1, C104.2, IC12.9 (VSS2_1), IC12.10 (VSS2_2), IC12.15 (VSS2_3), PS12.3 (-VOUT_1), PS12.4 (-VOUT_2)
/PH_U_H: IC8.2 (VI-); also elsewhere on the board
/PH_U_L: IC8.1 (VI+); also elsewhere on the board
/PH_U_L_D: D14.1 (K); also elsewhere on the board
/PH_U_L_G: IC8.11 (VOUT); also elsewhere on the board
/PH_U_L_S: C55.1, C56.2, C62.1, IC8.16 (GND2), PS8.6 (0V); also elsewhere on the board
/PH_V_H: IC9.1 (VI+), IC10.2 (VI-); also elsewhere on the board
/PH_V_H_D: D7.1 (K); also elsewhere on the board
/PH_V_H_G: IC9.11 (VOUT); also elsewhere on the board
/PH_V_H_S: C66.1, C67.2, C73.1, IC9.16 (GND2), PS9.6 (0V); also elsewhere on the board
/PH_V_L: IC9.2 (VI-), IC10.1 (VI+); also elsewhere on the board
/PH_V_L_D: D9.1 (K); also elsewhere on the board
/PH_V_L_G: IC10.11 (VOUT); also elsewhere on the board
/PH_V_L_S: C77.1, C78.2, C84.1, IC10.16 (GND2), PS10.6 (0V); also elsewhere on the board
/PH_W_H: IC11.1 (VI+), IC12.2 (VI-); also elsewhere on the board
/PH_W_H_D: D11.1 (K); also elsewhere on the board
/PH_W_H_G: IC11.11 (VOUT); also elsewhere on the board
/PH_W_H_S: C88.1, C89.2, C95.1, IC11.16 (GND2), PS11.6 (0V); also elsewhere on the board
/PH_W_L: IC11.2 (VI-), IC12.1 (VI+); also elsewhere on the board
/PH_W_L_D: D13.1 (K); also elsewhere on the board
/PH_W_L_G: IC12.11 (VOUT); also elsewhere on the board
/PH_W_L_S: C99.1, C100.2, C106.1, IC12.16 (GND2), PS12.6 (0V); also elsewhere on the board
/READY: IC8.7 (READY), IC9.7 (READY), IC10.7 (READY), IC11.7 (READY), IC12.7 (READY); also elsewhere on the board
/RESET: IC8.5 (~RESET), IC9.5 (~RESET), IC10.5 (~RESET), IC11.5 (~RESET), IC12.5 (~RESET); also elsewhere on the board
unnamed: D7.2 (A), R41.1
unnamed: D9.2 (A), R51.1
unnamed: D11.2 (A), R61.1
unnamed: D13.2 (A), R71.1
unnamed: D14.2 (A), R31.1
unnamed: C62.2, IC8.14 (DESAT), R30.2, R31.2
unnamed: C73.2, IC9.14 (DESAT), R40.2, R41.2
unnamed: C84.2, IC10.14 (DESAT), R50.2, R51.2
unnamed: C95.2, IC11.14 (DESAT), R60.2, R61.2
unnamed: C106.2, IC12.14 (DESAT), R70.2, R71.2

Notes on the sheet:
Keep close to gate drivers, decoupling caps

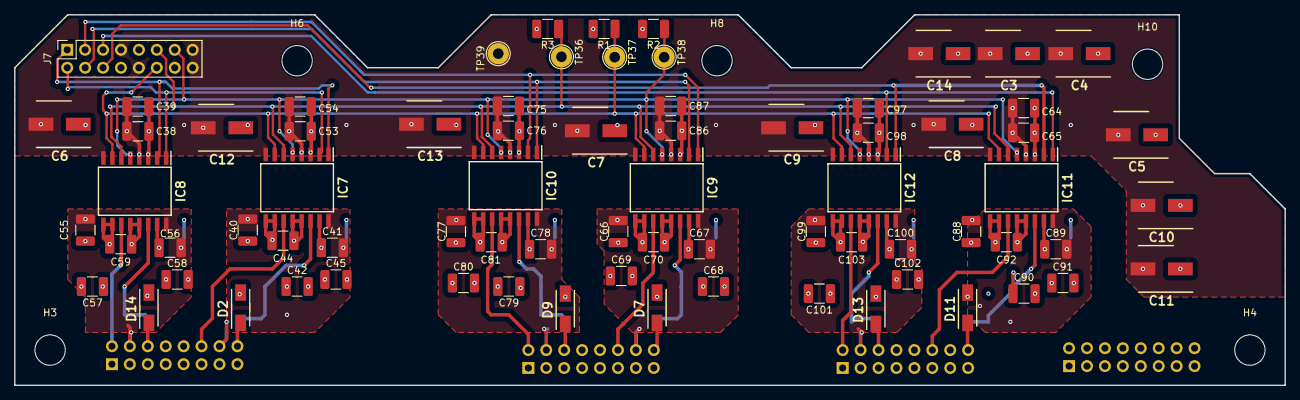
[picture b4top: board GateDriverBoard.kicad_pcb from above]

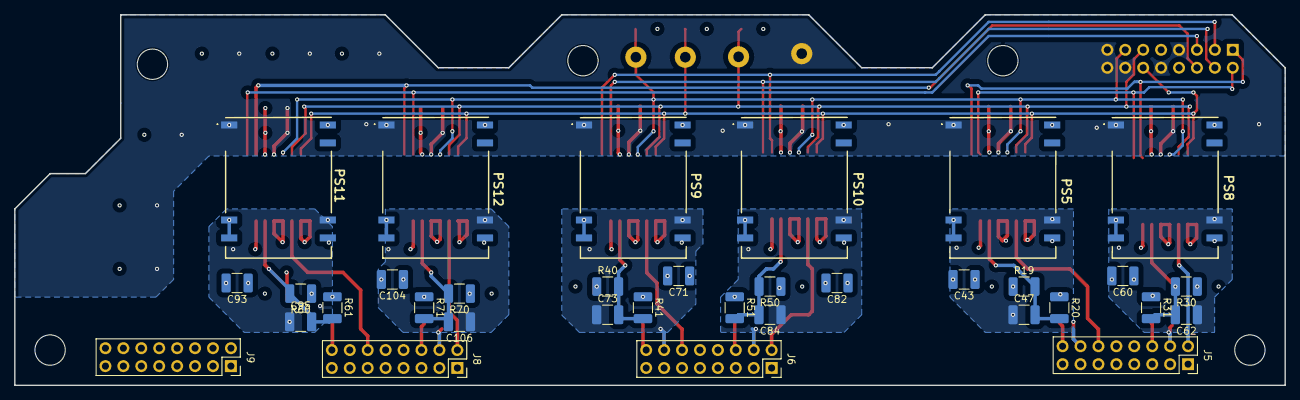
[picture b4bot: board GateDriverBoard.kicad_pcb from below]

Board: 6 copper layers, 180.0 x 52.5 mm, 113 parts (34 on the bottom side), 54 nets.

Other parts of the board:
J9: Conn_02x08_Counter_Clockwise; PinSocket_2x08_P2.54mm_Vertical
